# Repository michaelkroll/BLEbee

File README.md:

### BLEbee

The MIT License (MIT)
Copyright (c) 2012-2014 Dr. Michael Kroll
 
Permission is hereby granted, free of charge, to any person obtaining a copy of this software and associated 
documentation files (the "Software"), to deal in the Software without restriction, including without limitation 
the rights to use, copy, modify, merge, publish, distribute, sublicense, and/or sell copies of the Software, 
and to permit persons to whom the Software is furnished to do so, subject to the following conditions:
 
The above copyright notice and this permission notice shall be included in all copies or substantial portions of the Software.
 
THE SOFTWARE IS PROVIDED "AS IS", WITHOUT WARRANTY OF ANY KIND, EXPRESS OR IMPLIED, INCLUDING BUT NOT 
LIMITED TO THE WARRANTIES OF MERCHANTABILITY, FITNESS FOR A PARTICULAR PURPOSE AND NONINFRINGEMENT. IN 
NO EVENT SHALL THE AUTHORS OR COPYRIGHT HOLDERS BE LIABLE FOR ANY CLAIM, DAMAGES OR OTHER LIABILITY, 
WHETHER IN AN ACTION OF CONTRACT, TORT OR OTHERWISE, ARISING FROM, OUT OF OR IN CONNECTION WITH THE 
SOFTWARE OR THE USE OR OTHER DEALINGS IN THE SOFTWARE.

### Content

The final design of the BLEBee v1.0.0 Rev.B. looks as on the illustration below. Please use the pinout as illustrated. 

http://www.mkroll.mobi

http://forum.mkroll.mobi

This repository contains the eagle design files as well as the firmware source code which are needed modify and rebuild the firmware. The hexfiles are included as well. Moreover I added the Arduino Sketches from my blog to this repository as well.

Notes for BLEbee 1.0.0:
-----

-The Eagle design files are created using Eagle v6.4.0

-The Firmware v1.0.0 for the BLE112 module on the BLEbee was created and compiled for the Bluegiga BLE112 SDK v1.1.1-b71

-The Firmware v1.0.1 for the BLE112 module on the BLEbee was created and compiled for the Bluegiga BLE112 SDK v1.2.1-b91

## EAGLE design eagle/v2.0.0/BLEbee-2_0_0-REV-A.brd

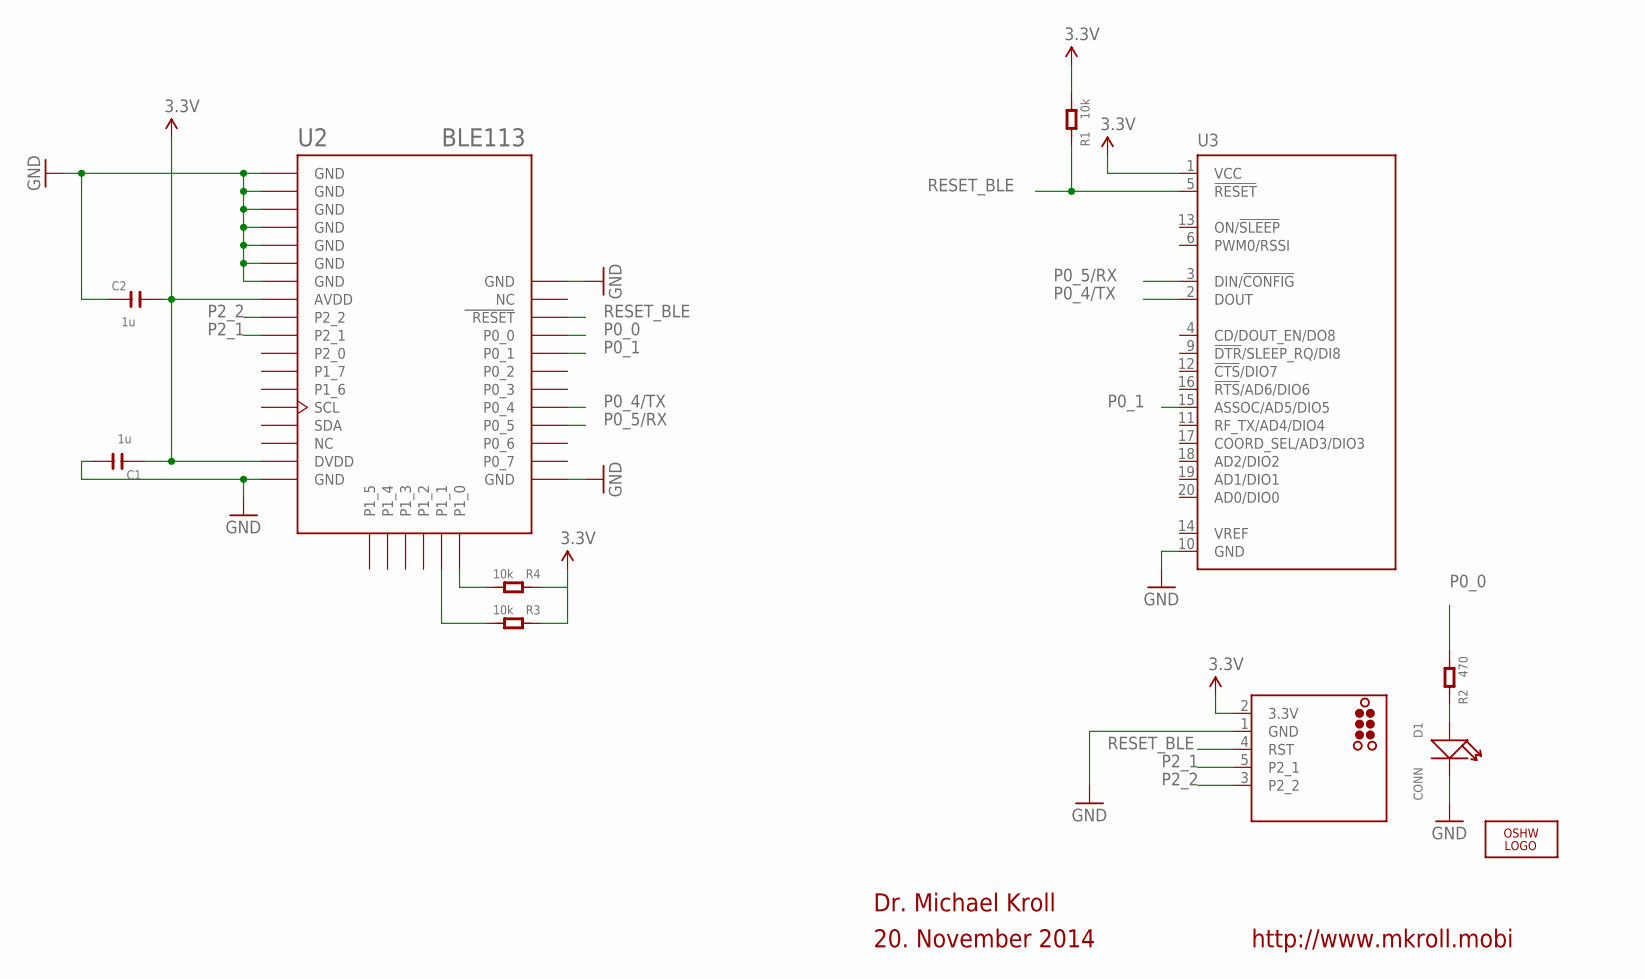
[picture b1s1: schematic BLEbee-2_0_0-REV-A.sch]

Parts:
C1, C2: 1u; C0603
D1: CONN; LED0603
J1: TC2030-CC-DEBUGGER; TC2030-MCP-NL
LOGO1: LOGO-OSHW-6MILX0100-NT; OSHW_6X100_NOTEXT
R1, R3, R4: 10k; R0603
R2: 470; R0603
U2: BLE113; BLE113-A
U3: MODULE_BEE-XBEE-DIP; MODULE_20P-DIP-2.0-W/-SILK

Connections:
3.3V: C1.2, C2.1, J1.2 (3.3V), R1.2, R3.1, R4.1, U2.AVDD, U2.DVDD, U3.1 (VCC)
GND: C1.1, C2.2, D1.-, J1.1 (GND), U2.GND, U2.GND@2 (GND), U2.GND@3 (GND), U2.GND@4 (GND), U2.GND@5 (GND), U2.GND@6 (GND), U2.GND@7 (GND), U2.GND@8 (GND), U2.GND@9 (GND), U2.GND@10 (GND), U3.10 (GND)
unnamed: D1.+, R2.1
unnamed: R4.2, U2.P1_0
unnamed: R3.2, U2.P1_1
P0_0: R2.2, U2.P0_0
P0_1: U2.P0_1, U3.15 (ASSOC/AD5/DIO5)
P0_4/TX: U2.P0_4, U3.2 (DOUT)
P0_5/RX: U2.P0_5, U3.3 (DIN/!CONFIG)
P2_1: J1.5 (P2_1), U2.P2_1
P2_2: J1.3 (P2_2), U2.P2_2
RESET_BLE: J1.4 (RST), R1.1, U2.RESET, U3.5 (!RESET)

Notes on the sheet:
Dr. Michael Kroll
20. November 2014
http://www.mkroll.mobi

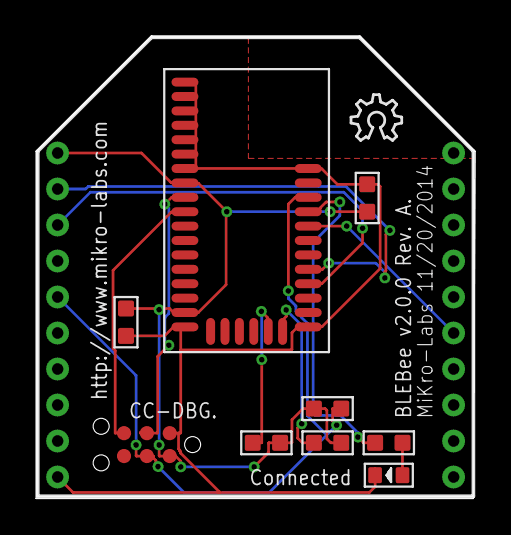
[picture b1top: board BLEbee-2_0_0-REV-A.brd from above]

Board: 4 copper layers, 24.4 x 25.7 mm, 12 parts (1 on the bottom side), 12 nets.

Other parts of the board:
U$1: MIKROLABS-LOGO

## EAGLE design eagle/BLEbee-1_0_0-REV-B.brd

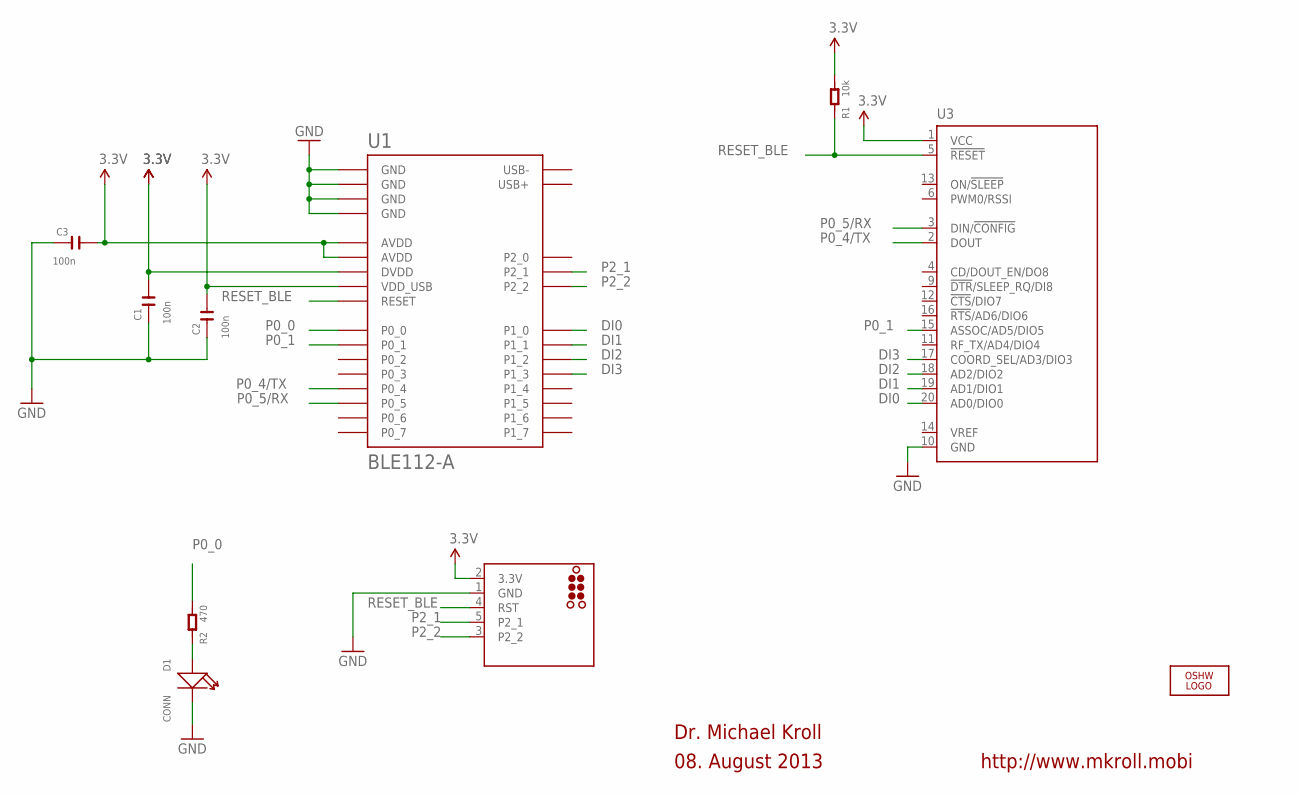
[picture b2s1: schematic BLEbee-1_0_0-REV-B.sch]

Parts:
C1, C2, C3: 100n; C0603
D1: CONN; LED0603
J1: TC2030-CC-DEBUGGER; TC2030-MCP-NL
LOGO1: LOGO-OSHW-6MILX0100-NT; OSHW_6X100_NOTEXT
R1: 10k; R0603
R2: 470; R0603
U1: BLE112-A
U3: MODULE_BEE-XBEE-DIP; MODULE_20P-DIP-2.0-W/-SILK

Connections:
3.3V: C1.1, C2.1, C3.1, J1.2 (3.3V), R1.2, U1.AVDD1 (AVDD), U1.AVDD2 (AVDD), U1.DVDD, U1.VDD_USB, U3.1 (VCC)
DI0: U1.P1_0, U3.20 (AD0/DIO0)
DI1: U1.P1_1, U3.19 (AD1/DIO1)
DI2: U1.P1_2, U3.18 (AD2/DIO2)
DI3: U1.P1_3, U3.17 (COORD_SEL/AD3/DIO3)
GND: C1.2, C2.2, C3.2, D1.-, J1.1 (GND), U1.GND1 (GND), U1.GND2 (GND), U1.GND3 (GND), U1.GND4 (GND), U3.10 (GND)
unnamed: D1.+, R2.1
P0_0: R2.2, U1.P0_0
P0_1: U1.P0_1, U3.15 (ASSOC/AD5/DIO5)
P0_4/TX: U1.P0_4, U3.2 (DOUT)
P0_5/RX: U1.P0_5, U3.3 (DIN/!CONFIG)
P2_1: J1.5 (P2_1), U1.P2_1
P2_2: J1.3 (P2_2), U1.P2_2
RESET_BLE: J1.4 (RST), R1.1, U1.RESET, U3.5 (!RESET)

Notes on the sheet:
Dr. Michael Kroll
08. August 2013
http://www.mkroll.mobi

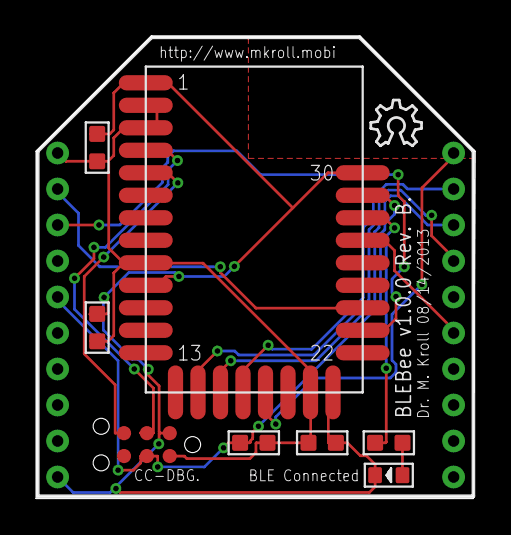
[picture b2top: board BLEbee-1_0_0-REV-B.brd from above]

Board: 4 copper layers, 24.4 x 25.7 mm, 10 parts (0 on the bottom side), 14 nets.

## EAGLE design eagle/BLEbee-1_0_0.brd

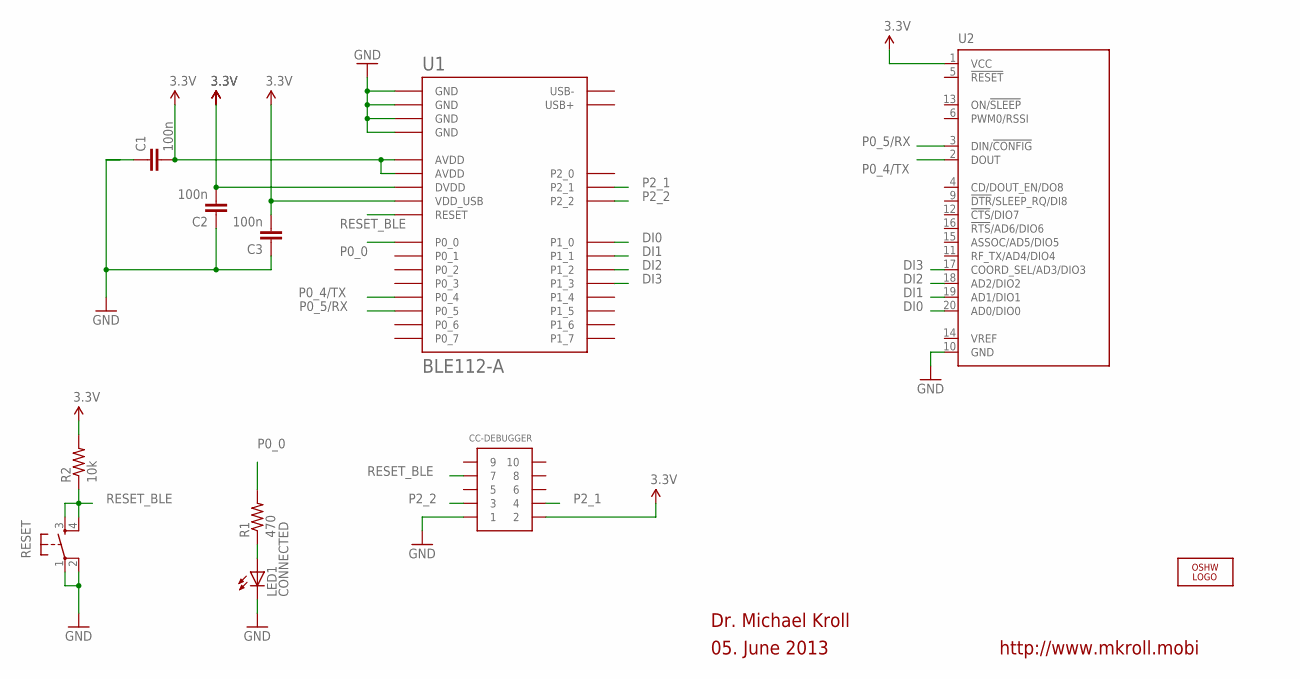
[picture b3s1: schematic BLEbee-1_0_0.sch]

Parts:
C1, C2, C3: 100n; 0402-CAP
CC-DEBUGGER: CONN_5-2-FTSH-V; FTSH-105-DV
LED1: CONNECTED; LED-0603
LOGO1: LOGO-OSHW-6MILX0100-NT; OSHW_6X100_NOTEXT
R1: 470; 0402-RES
R2: 10k; 0402-RES
RESET: TAC_SWITCHSMD; TACTILE_SWITCH_SMD
U1: BLE112-A
U2: BEE-XBEE-DIP; 20P-DIP-2.0-W/-SILK

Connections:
3.3V: C1.2, C2.2, C3.2, CC-DEBUGGER.2, R2.2, U1.AVDD1 (AVDD), U1.AVDD2 (AVDD), U1.DVDD, U1.VDD_USB, U2.1 (VCC)
DI0: U1.P1_0, U2.20 (AD0/DIO0)
DI1: U1.P1_1, U2.19 (AD1/DIO1)
DI2: U1.P1_2, U2.18 (AD2/DIO2)
DI3: U1.P1_3, U2.17 (COORD_SEL/AD3/DIO3)
GND: C1.1, C2.1, C3.1, CC-DEBUGGER.1, LED1.C, RESET.1, RESET.2, U1.GND1 (GND), U1.GND2 (GND), U1.GND3 (GND), U1.GND4 (GND), U2.10 (GND)
unnamed: LED1.A, R1.1
P0_0: R1.2, U1.P0_0
P0_4/TX: U1.P0_4, U2.2 (DOUT)
P0_5/RX: U1.P0_5, U2.3 (DIN/!CONFIG)
P2_1: CC-DEBUGGER.4, U1.P2_1
P2_2: CC-DEBUGGER.3, U1.P2_2
RESET_BLE: CC-DEBUGGER.7, R2.1, RESET.3, RESET.4, U1.RESET

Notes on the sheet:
Dr. Michael Kroll
05. June 2013
http://www.mkroll.mobi

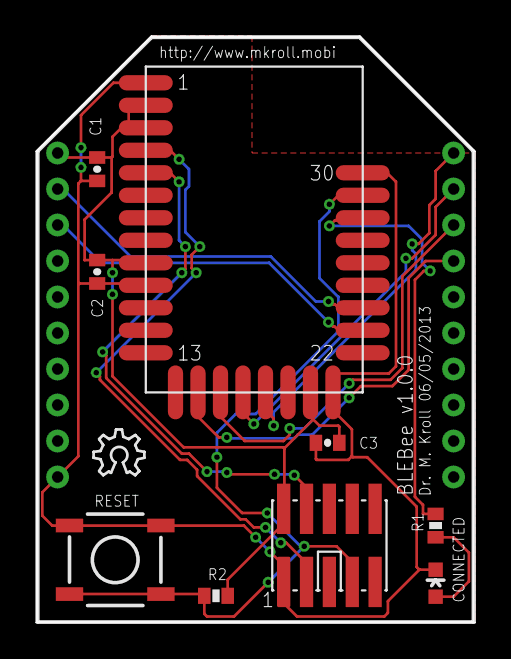
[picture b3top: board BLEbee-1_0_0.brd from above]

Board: 4 copper layers, 24.4 x 32.6 mm, 11 parts (0 on the bottom side), 13 nets.

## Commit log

2012-11-04 initial version commited to github.
2012-11-04 changed to contain the app versions necessary
2013-01-13 Project file updated.
2013-06-30 Design files, firmware files and Arduino FIO v3 Arduino Sketch added.
2013-07-03 Demo Sketch for the Arduino FIO added.
2013-08-18 New firmware version added.
2013-08-18 spelling changed.
2013-08-18 tab removed.
2013-08-18 new pinout image added.
2013-08-18 renamed.
2013-08-18 pin out added to the README.me file.
2013-08-18 unused method removed.
2013-08-22 wrong pin descriptions for the connect led and the assoc pin fixed.
2013-08-30 updated to the v1.0.0 Revision B BLEBee.
2013-08-30 BLEBee v1.0.0 Revision B schematic and board file added.
2013-08-30 Arduino FIO v3 Sample Sketch added.
2013-08-30 Arduino Leonardo with Wirless Proto Shield sample added.
2013-09-01 Test Sketch for the Arduino FIO.
2013-09-21 Added some performance related changes proposed by Phan Shi Wen.
2013-09-22 Changed the name of the BLEBee from bee to Bee.
2013-09-22 Old prototype files removed.
2013-09-23 License changed to MIT
2013-09-25 last changes for the production run.
2013-12-30 latest file changes.
2014-01-06 Added baudrates 57600 and 112500 which can be set by writing 0x05 and 0x06 to the Baudrate characteristic.
2014-07-26 new input shield sample added.
2014-08-13 project file for the BLE113 added.
2014-11-19 revompiled the firmware file.
2014-12-07 Version 2.0.0 of the firmware prepared for the new hardware revision v2.0.0 using the BLE113.
2015-04-26 Latest version with the new SDK1.3.2 tested.
2015-05-05 New test sketch added.
2015-05-05 Eagle design files for the new BLEBee v2.0.0 added.
2015-07-07 New Arduino Sketch Added to run the BLEBee v2.0.0 using the Wireless Proto Shield on an Arduino Leonardo.
2015-07-08 Backport of the BLEBee v1.0.0 firmware to BLEBee v2.0.0
2015-07-08 Added a new description of the firmware.

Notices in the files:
parts and their libraries:
Tag-Connect: ©2009 ROFA.cz - modified and updated by Robert Darlington ‹rdarlington@gmail.com›
Tag-Connect: ©2013 http://www.mkroll.mobi - modified and updated by Dr. Michael Kroll ‹dr.michael.kroll@gmail.com›
